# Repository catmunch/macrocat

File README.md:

# Macrocat

A cat like macro keyboard/numpad.

## Resources
- [Designer Spreadsheet](https://docs.google.com/spreadsheets/d/15iPMkPPelqXUuJzfWze6s_fHAjqMbbhKXIEQs6-oLG8/edit#gid=0)
- [QMK Docs](https://docs.qmk.fm/#/)
- [ai03](https://wiki.ai03.com/books)
- [Keyboard Layout Editor](http://www.keyboard-layout-editor.com/#/gists/0d682a6dd41d7de2ae32d8b280f85d39)
- [ai03 Plate Generator](https://kbplate.ai03.com/)
- [Keyswitch KiCAD Library](https://github.com/perigoso/keyswitch-kicad-library) Licensed in CC-BY-SA 4.0

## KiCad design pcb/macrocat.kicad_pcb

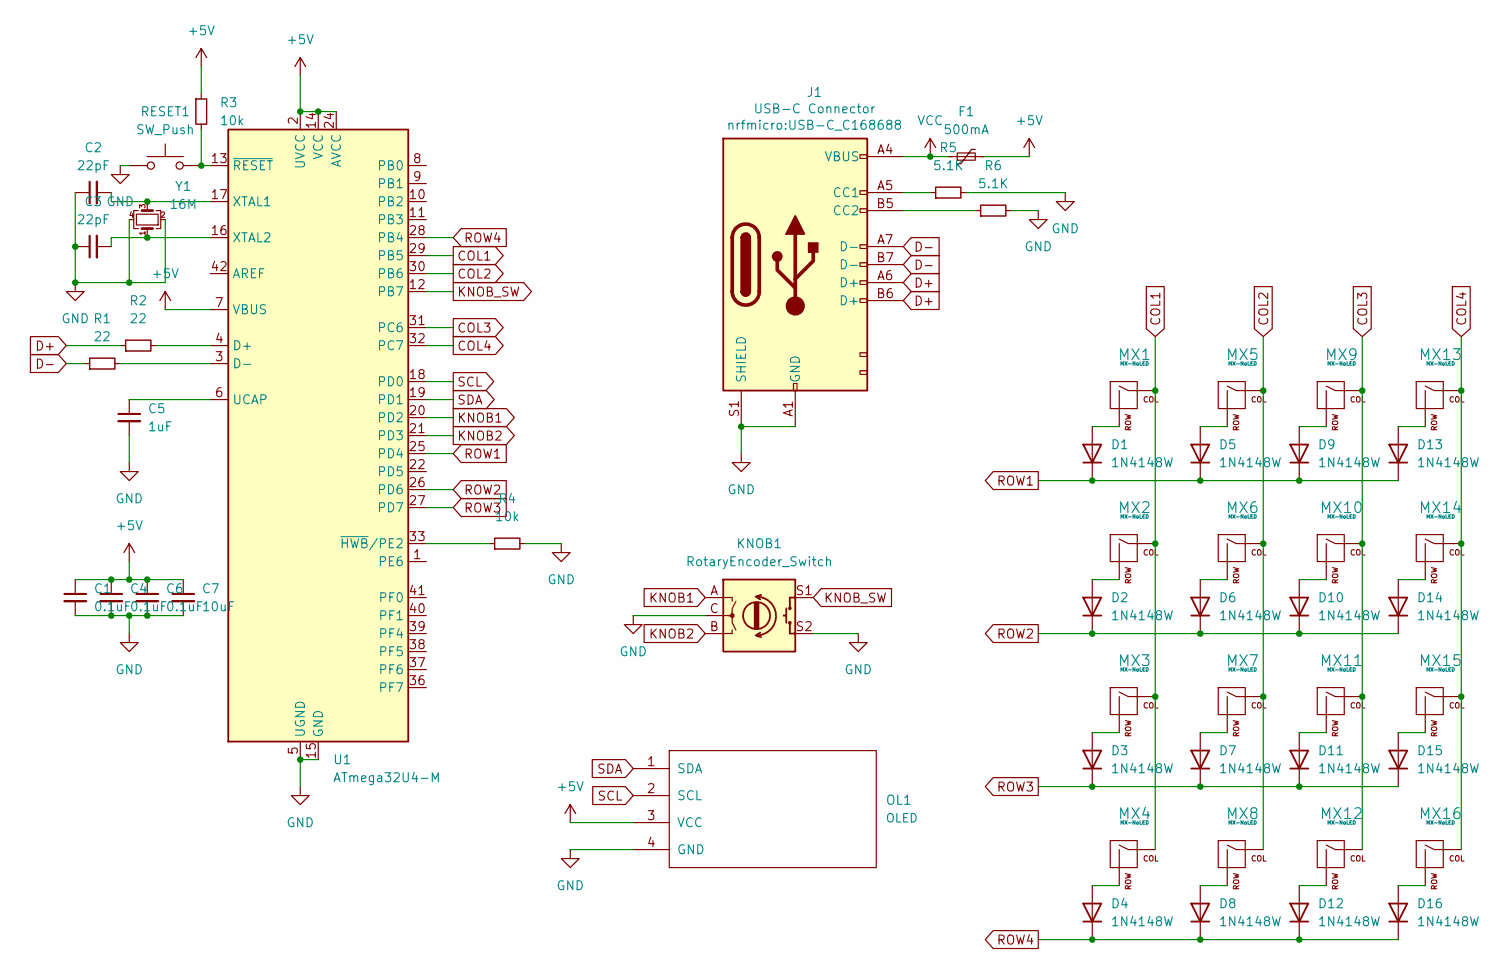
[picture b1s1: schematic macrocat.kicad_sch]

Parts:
C1, C4, C6: 0.1uF; C_0805_2012Metric
C2, C3: 22pF; C_0805_2012Metric
C5: 1uF; C_0805_2012Metric
C7: 10uF; C_0805_2012Metric
D1, D2, D3, D4, D5, D6, D7, D8, D9, D10, D11, D12, D13, D14, D15, D16: 1N4148W; D_SOD-123_back
F1: 500mA; Fuse_1206_3216Metric
J1: USB-C Connector; USB-C_C168688
KNOB1: RotaryEncoder_Switch; RotaryEncoder_Alps_EC11E-Switch_Vertical_H20mm
MX1, MX2, MX3, MX4, MX5, MX6, MX7, MX8, MX9, MX10, MX11, MX12, MX13, MX14, MX15, MX16: MX-NoLED; MXOnly-1U-Hotswap
OL1: OLED; OLED_v2
R1, R2: 22; R_0805_2012Metric
R3, R4: 10k; R_0805_2012Metric
R5, R6: 5.1K; R_0805_2012Metric
RESET1: SW_Push; SW_DIP_SPSTx01_Slide_6.7x4.1mm_W6.73mm_P2.54mm_LowProfile_J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
U1: ATmega32U4-M; QFN-44-1EP_7x7mm_P0.5mm_EP5.2x5.2mm
Y1: 16M; Crystal_SMD_3225-4Pin_3.2x2.5mm

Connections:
+5V: C1.1, C4.1, C6.1, C7.1, F1.2, OL1.3 (VCC), R3.1, U1.2 (UVCC), U1.7 (VBUS), U1.14 (VCC), U1.24 (AVCC), U1.34 (VCC), U1.44 (AVCC)
COL1: MX1.1 (COL), MX2.1 (COL), MX3.1 (COL), MX4.1 (COL), U1.29 (PB5)
COL2: MX5.1 (COL), MX6.1 (COL), MX7.1 (COL), MX8.1 (COL), U1.30 (PB6)
COL3: MX9.1 (COL), MX10.1 (COL), MX11.1 (COL), MX12.1 (COL), U1.31 (PC6)
COL4: MX13.1 (COL), MX14.1 (COL), MX15.1 (COL), MX16.1 (COL), U1.32 (PC7)
D+: J1.A6 (D+), J1.B6 (D+), R2.1
D-: J1.A7 (D-), J1.B7 (D-), R1.1
GND: C1.2, C2.1, C3.1, C4.2, C5.2, C6.2, C7.2, J1.A1 (GND), J1.S1 (SHIELD), KNOB1.C, KNOB1.S2, OL1.4 (GND), R4.2, R5.2, R6.2, RESET1.1, U1.5 (UGND), U1.15 (GND), U1.23 (GND), U1.35 (GND), U1.43 (GND), U1.45 (GND), Y1.2, Y1.4
KNOB1: KNOB1.A, U1.20 (PD2)
KNOB2: KNOB1.B, U1.21 (PD3)
KNOB_SW: KNOB1.S1, U1.12 (PB7)
unnamed: C2.2, U1.17 (XTAL1), Y1.3
unnamed: C3.2, U1.16 (XTAL2), Y1.1
unnamed: C5.1, U1.6 (UCAP)
unnamed: D1.2 (A), MX1.2 (ROW)
unnamed: D2.2 (A), MX2.2 (ROW)
unnamed: D3.2 (A), MX3.2 (ROW)
unnamed: D4.2 (A), MX4.2 (ROW)
unnamed: D5.2 (A), MX5.2 (ROW)
unnamed: D6.2 (A), MX6.2 (ROW)
unnamed: D7.2 (A), MX7.2 (ROW)
unnamed: D8.2 (A), MX8.2 (ROW)
unnamed: D9.2 (A), MX9.2 (ROW)
unnamed: D10.2 (A), MX10.2 (ROW)
unnamed: D11.2 (A), MX11.2 (ROW)
unnamed: D12.2 (A), MX12.2 (ROW)
unnamed: D13.2 (A), MX13.2 (ROW)
unnamed: D14.2 (A), MX14.2 (ROW)
unnamed: D15.2 (A), MX15.2 (ROW)
unnamed: D16.2 (A), MX16.2 (ROW)
unnamed: J1.A5 (CC1), R5.1
unnamed: J1.B5 (CC2), R6.1
unnamed: R1.2, U1.3 (D-)
unnamed: R2.2, U1.4 (D+)
unnamed: R3.2, RESET1.2, U1.13 (~RESET)
unnamed: R4.1, U1.33 (~HWB/PE2)
ROW1: D1.1 (K), D5.1 (K), D9.1 (K), D13.1 (K), U1.25 (PD4)
ROW2: D2.1 (K), D6.1 (K), D10.1 (K), D14.1 (K), U1.26 (PD6)
ROW3: D3.1 (K), D7.1 (K), D11.1 (K), D15.1 (K), U1.27 (PD7)
ROW4: D4.1 (K), D8.1 (K), D12.1 (K), D16.1 (K), U1.28 (PB4)
SCL: OL1.2 (SCL), U1.18 (PD0)
SDA: OL1.1 (SDA), U1.19 (PD1)
VCC: F1.1, J1.A4 (VBUS)

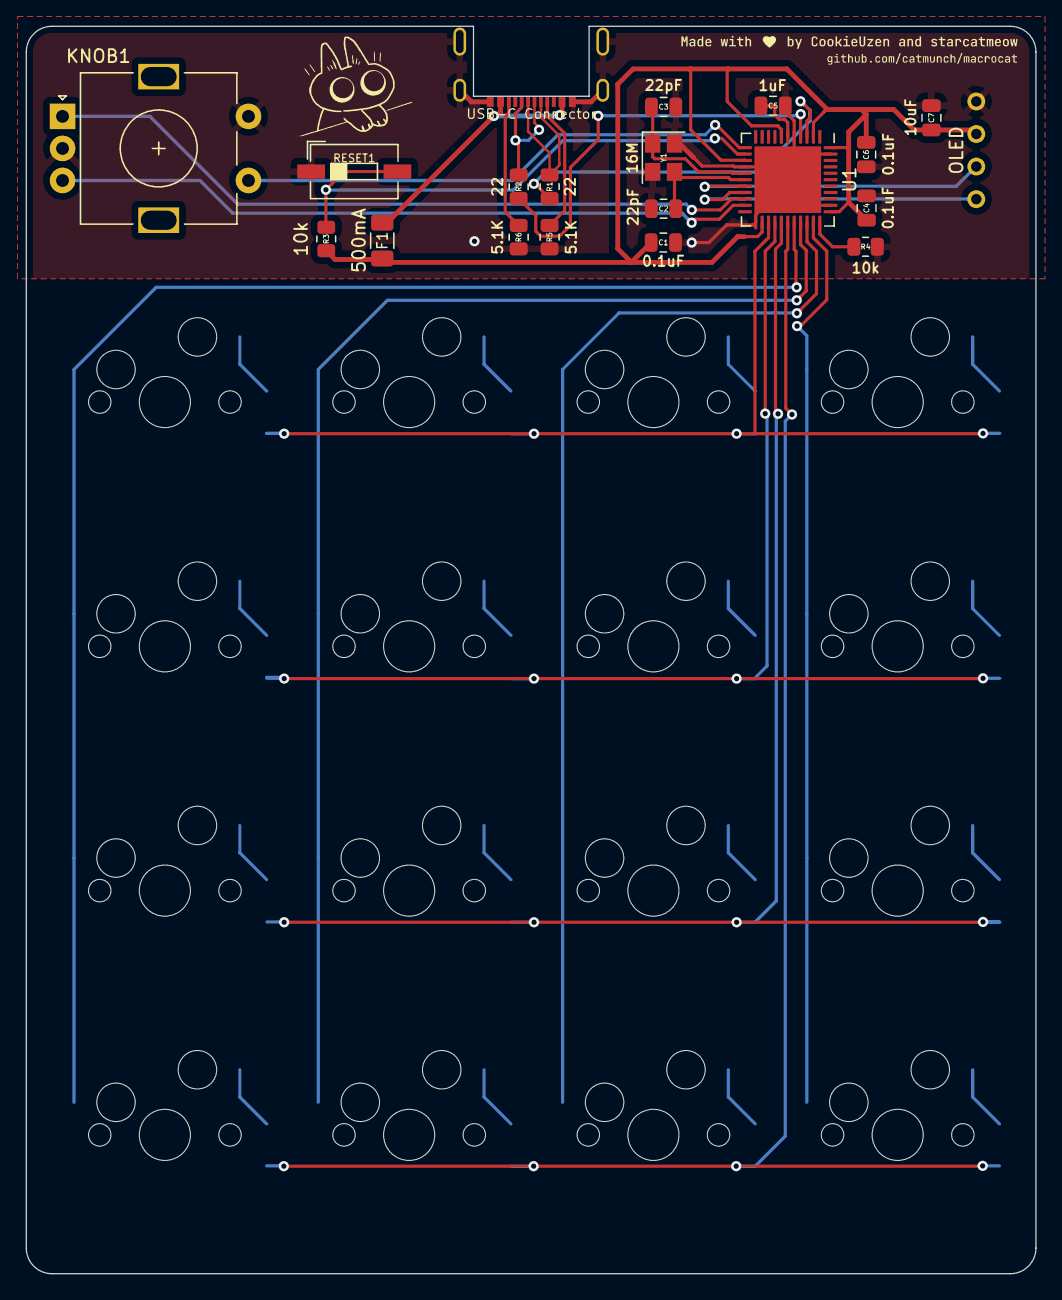
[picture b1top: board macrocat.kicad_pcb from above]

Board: 2 copper layers, 78.7 x 97.3 mm, 52 parts (0 on the bottom side), 43 nets.

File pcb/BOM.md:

BOM

|Designator|Name|Quantity|Link|
|----------|----|--------|----|
|U1|ATmega32U4-MU|1||
|D1-D16|1N4148W SOD-123|16||
|MX1-MX16|Kailh Hotswap Socket|16||
|R1-R2|22 Ohm 0805 Resistor|2||
|R3-R4|10k Ohm 0805 Resistor|2||
|R5-R6|5.1k Ohm 0805 Resistor|2||
|C1,C4,C6|0.1uF 0805 Capacitor|3||
|C2,C3|22pF 0805 Capacitor|2||
|C5|1uF 0805 Capacitor|1||
|C7|10uF 0805 Capacitor|1||
|F1|500mA 1206 Fuse|1||
|Y1|16MHz 3225 Crystal|1||
|J1|USB-C Mid Mount Connector|1||
|RESET1|6.7*4.1mm Button|1||
|KNOB1|EC11 Rotary Encoder|1||
|OL1|4-pin 2.54mm Socket|1||

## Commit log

2022-06-14 README
2022-06-14 add footprint libs
2022-06-14 added resources
2022-06-14 initial layout + plate
2022-06-15 finish schematic diagram
2022-06-15 finish pcb layout
2022-06-15 routed by freerouter
2022-06-15 fix some bug in pcb
2022-06-15 refill the ground
2022-06-15 adjust some figures on pcb
2022-06-15 change MX_Alps_Hybrid submodule url to the fork one
2022-06-15 fix submodule remote url
2022-06-15 plate design 1.0
2022-06-15 optimize mcu part wiring
2022-06-15 plate design 1.1
2022-06-17 add some cat
2022-06-17 plate design 1.2
2022-06-17 plate design 1.2.1
    Fixed some major bugs, added screw holes on bottom case, moved to M2.5
    screws
2022-06-17 change mcu to atmega32u4-mu
2022-06-17 add plate screw holes :)
2022-06-18 plate design 1.2.2
    Changed some variable names
2022-06-18 case design 1.2.3
    Add top housing screws
2022-06-18 case design 1.2.4
    Added type c port
2022-06-18 Case design 1.2.5
    increase type c hole
2022-06-18 reduce side clearance
2022-06-18 increase side clearance
2022-06-20 plate design 1.2.6
2022-06-20 seperated openscad files
2022-06-28 create 3d model
2022-06-28 migrate the stl to git lfs
2022-06-28 plate v0.1
    Made the plate without the surronding casing for support.
2022-06-29 plate update + top case
2022-06-30 Minor fixes to margins and keycap spacing
2022-07-01 Bottom case design
2022-07-24 added screw holes, tweaked variables
2022-07-25 added type c hole and fixed plate screw holes
2022-07-25 add weight
2022-07-25 Added render script, fixed type c cutout on plate
2022-07-25 lfs + deepen engraving
2022-07-25 rev 2.0.0
